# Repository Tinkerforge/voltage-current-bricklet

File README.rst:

Voltage/Current Bricklet
========================

This repository contains the firmware source code and the hardware design
files. The documentation generator configs can be found at
https://github.com/Tinkerforge/generators

Repository Content
------------------

software/:
 * examples/: Examples for all supported languages
 * build/: Compiled files
 * src/: Source code of firmware
 * Makefile: Makefile to build project

hardware/:
 * Contains KiCad project files and additionally schematics as PDF

datasheets/:
 * Contains datasheets for sensors and complex ICs that are used

Hardware
--------

The hardware is designed with the open source EDA Suite KiCad
(http://www.kicad.org). Before you are able to open the files,
you have to install the Tinkerforge kicad-libraries
(https://github.com/Tinkerforge/kicad-libraries). You can either clone
them directly in hardware/ or clone them in a separate folder and
symlink them into hardware/
(ln -s kicad_path/kicad-libraries project_path/hardware). After that you
can open the .pro file in hardware/ with KiCad and from there view and
modify the schematics and the PCB layout.

Software
--------

If you want to do your own Brick/Bricklet firmware development we highly
recommend that you use our build environment setup script and read the
tutorial (https://www.tinkerforge.com/en/doc/Tutorials/Tutorial_Build_Environment/Tutorial.html).

To compile the C code we recommend you to install the newest GNU Arm Embedded
Toolchain (https://launchpad.net/gcc-arm-embedded/+download).
You also need to install bricklib (https://github.com/Tinkerforge/bricklib)
and brickletlib (https://github.com/Tinkerforge/brickletlib).

You can either clone it directly in software/src/ or clone it in a
separate folder and symlink it into software/src/
(ln -s bricklib_path/bricklib project_path/software/src/ and
ln -s brickletlib_path/brickletlib project_path/software/src/).
Finally make sure to have CMake installed
(http://www.cmake.org/cmake/resources/software.html).

After that you can build the firmware by invoking make in software/.
The firmware (.bin) can then be found in software/build/ and uploaded
with brickv (click button "Flashing" on start screen).

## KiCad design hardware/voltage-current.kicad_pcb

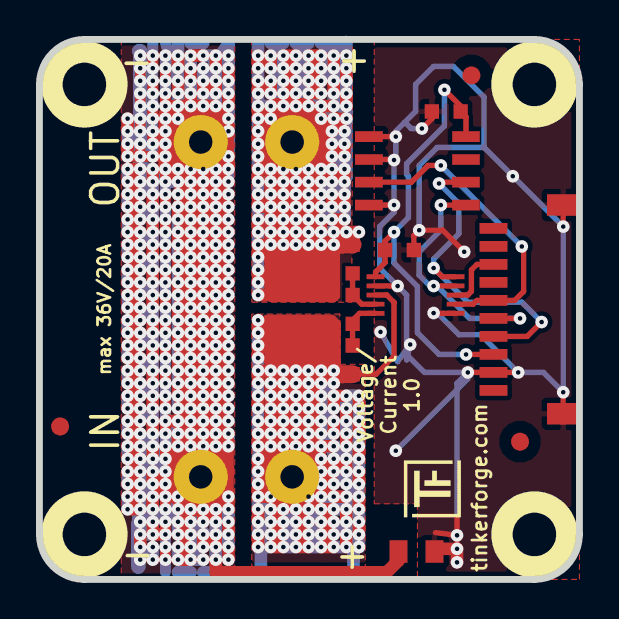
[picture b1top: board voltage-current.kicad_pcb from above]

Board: 2 copper layers, 30.0 x 30.0 mm, 25 parts (0 on the bottom side), 11 nets.

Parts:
C1, C2, C3: 100nF; C0603
Fiducial_Mark: VAL**; Fiducial_Mark
Fiducial_Mark#2, Fiducial_Mark#3: VAL**; Fiducial_Mark
P1: CON-SENSOR
P2: Input; AKL_5_2_508_black
P3: Output; AKL_5_2_508_black
P4, P5, P6, P7: TST; SOLDER_PAD
R1, R2: 10; R0603
R3: 4m; R2512
R4: 0; R0805
U1: M24C64; SOIC8
U2: INA226; MSOP10-0.5
U3, U4, U5, U6: DRILL; DRILL_NP
VAL: CE_5mm
VAL#2: WEEE_7mm

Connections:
Alert: P1.8, U2.3
GND: C1.2, C2.1, P1.2, P1.EP, R4.2, U1.1, U1.2, U1.4, U2.1, U2.7
unnamed: C3.1, R2.1, U2.9
unnamed: C3.2, R1.1, U2.10
unnamed: P1.6, U1.3, U2.2
unnamed: P2.1, P4.1, R1.2, R3.2, U2.8
unnamed: P2.2, P3.1, P5.1, P7.1, R4.1
unnamed: P3.2, P6.1, R2.2, R3.1
SCL: P1.4, U1.6, U2.5
SDA: P1.5, U1.5, U2.4
VCC: C1.1, C2.2, P1.3, U1.8, U2.6

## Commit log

2012-12-18 Add support for protocol 2.0
2012-12-18 Add sanity checks for calibration and configuration
2012-12-18 Add sanity checks for calibration and configuration
    Conflicts:
    software/src/voltage-current.c
2012-12-19 add hardware files
2012-12-19 Add c, csharp, delphi, java, php, python and ruby examples for v1.x.y
2012-12-19 Add sanity checks for calibration and configuration
    Conflicts:
    software/src/voltage-current.c
    Conflicts:
    software/src/voltage-current.c
2012-12-20 Save calibration on set_calibraiton, remove prints
2012-12-20 Save calibration on set_calibraiton, remove prints
    Conflicts:
    software/src/voltage-current.c
2012-12-21 Add correct device identifier
2012-12-21 Add c, csharp, delphi, java, php, python and ruby examples for v1.x.y
    Conflicts:
    software/src/voltage-current.h
2012-12-21 Add examples for protocol 2.0
2012-12-21 Use void* cast for cb
2012-12-21 Add .gitignore
2013-01-04 Avoid compiler warning in C/C++ examples
2013-01-09 Use specific device object for callbacks
2013-01-15 Use version 2.0.1 for update purposes, version 2.0.0 was accidentially shown in 1.0.0
2013-01-17 Make Java examples compatible to new listener approach
2013-01-28 Update outdated comment in Java example
2013-02-07 Use IPconnection disconnect explicitly in examples
2013-02-14 Fix debounce period in C# threshold example
2013-02-18 Add Visual Basic .NET examples
2013-05-15 Don't send threshold callback twice
    Fixed in brickletlib.
2013-07-31 Fix voltage and power reached callbacks, were send as current reached callback
2013-08-14 Add shell examples
2013-08-14 Do calculations in the calculation tick only
2013-08-21 windows: Don't trigger a build in generate_makefile.bat
    Also use normal make instead of a special named one.
2013-12-19 Fix wrong length for GetDebounce packet (through brickletlib)
2014-01-06 Add static assert for BrickContext size
2014-01-10 Add Perl examples
2014-01-15 php: Use const for constant values
2014-02-07 Add Mathematica examples
2014-02-10 perl: fixed namespace
2014-02-11 javascript: add examples
2014-02-18 javascript: examples fixed
2014-02-20 javascript: add html examples
2014-02-24 javascript: port 4280, startExample()
2014-02-28 javascript: Break long lines and cleanup whitespace
2014-03-05 Add LabVIEW examples
2014-03-06 labview: Add examples in LV2010 format
2014-03-25 matlab: add examples
2014-04-02 java: Unify constants style
2014-04-02 perl: Unify print style
2014-04-17 matlab: Adapt examples to new callback style
2014-04-17 matlab: Add parentheses to make pygments happy
2014-04-17 matlab: Fix string in Octave
2014-07-15 java: Replace System.console() usage with an Eclipse compatible pattern
2014-12-02 Use ReadLine instead of ReadKey for C# example
2015-02-13 vbnet: Use ReadLine instead of ReadKey
    Because ReadKey doesn't work with a pipe as stdin on the RED Brick.
2015-03-02 windows: Stop cmake from searching for mingw32-make.exe
    Using MinGW Makefiles as generator makes cmake search for mingw32-make.exe
    which might not be installed because GnuWin32's make.exe is used instead.
2015-03-26 checkin of latest hardware files
2015-04-09 c: Whitespace
2015-06-24 javascript: Clean up output creation
2015-07-25 Make JavaScript browser example textarea readonly
2015-07-27 Cleanup C/C++, C#, Java, Python and Ruby examples
2015-07-29 Reformat changelog
2015-08-07 Use full device class name in Python examples
2015-08-07 Use different values (voltage, current, power) in dfferent examples
2015-08-12 Fix minor warnings in C/C++ examples
2015-08-14 Cleanup Delphi examples
2015-08-18 Cleanup VB.NET examples
2015-08-19 Cleanup Perl examples
2015-09-10 Duplicate cmake call to fix bug during cmake creation
    Also, toolchain is now in bricklib.
2015-09-30 Generator based example cleanup
2015-11-12 matlab: Fix callback handling for R2014a
    http://undocumentedmatlab.com/blog/matlab-callbacks-for-java-events-in-r2014a
2015-11-24 Fix changelog
2015-11-25 Include date and commit into changelog
2016-05-18 c: Add missing device destroy call
2016-07-01 Make the change UID comment more explicit
2017-04-13 csharp: Adapt example
2017-04-21 shell: Adapt example
2017-06-02 octave: Use javaObject instead of deprecated java_new
2017-08-03 Add 3d information (final)
2017-08-03 Fix edge cuts
2017-08-03 Add 3d model (*.step & *.FCStd)
2017-11-30 Update examples from generator
2017-12-07 mathematica: Also generate .nb files
2018-02-02 Update examples
2018-02-19 javascript: Close div tag correctly
2018-02-20 Cleanup KiCad libraries config
    Ensure LibDir=kicad-libraries and LibName1=tinkerforge.
    Remove special library.
2018-05-24 perl: Use strict in examples
2018-07-11 Add Makefile with docker support
2018-07-11 Remove obsolete generate_makefile scripts
2018-07-11 Update directory structure and build instructions
2018-11-06 Add rust examples
2018-11-07 rust: Accept host names for ip connection, fix naming inconsistencies
2018-11-07 rust: Rename callback receivers.
2018-12-14 Add go examples.
2018-12-14 go: Fix printf parameters.
2018-12-18 go: Change import path.
2018-12-18 go: Change import path again.
2018-12-20 rust: Reformat examples.
2019-01-24 mqtt: Add examples.
2019-01-24 mqtt: Fix example header.
2019-01-24 mqtt: Remove executable bit in example permissions.
2019-01-24 go: Minor example fixes.
2019-01-24 mqtt: Minor example fixes.
2019-03-28 mqtt: Fix whitespace.
2019-08-22 c: Adapt to bindings changes
2020-01-13 examples: Use python3 input instead of python2 raw_input.
2020-01-13 examples: mqtt: Remove trailing whitespace.
2020-04-14 mqtt: Fix device name format
2021-10-25 Update KiCad link
    https://www.kicad.org/blog/2021/10/Avoid-links-to-former-kicad-domain/
2022-07-06 Add license files.

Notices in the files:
hardware/voltage-current.kicad_pcb:
Licensed under CERN OHL v.1.1
Copyright (©) 2011, B.Nordmeyer
Copyright Tinkerforge GmbH 2012.
This documentation describes Open Hardware and is licensed under the
CERN OHL v. 1.1.
